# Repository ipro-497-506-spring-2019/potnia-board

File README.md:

# potnia-board
These are the KiCad files for Potnia's PCB.

Release schedule:

|   Version |   Description |   Projected Date | ☑? |
| --------- |   ----------- |   -------------- | -- |
| v0| Super alpha |                                 March 1, 2019 | ☑ |
| v1| Ready for online review |                     March 8, 2019 | ☐ |
| v2| Ready to be sent off for first-round board |  March 15, 2019| ☐ |
| v3| Final revisions; this is a final board |      April 5, 2019 | ☐ |

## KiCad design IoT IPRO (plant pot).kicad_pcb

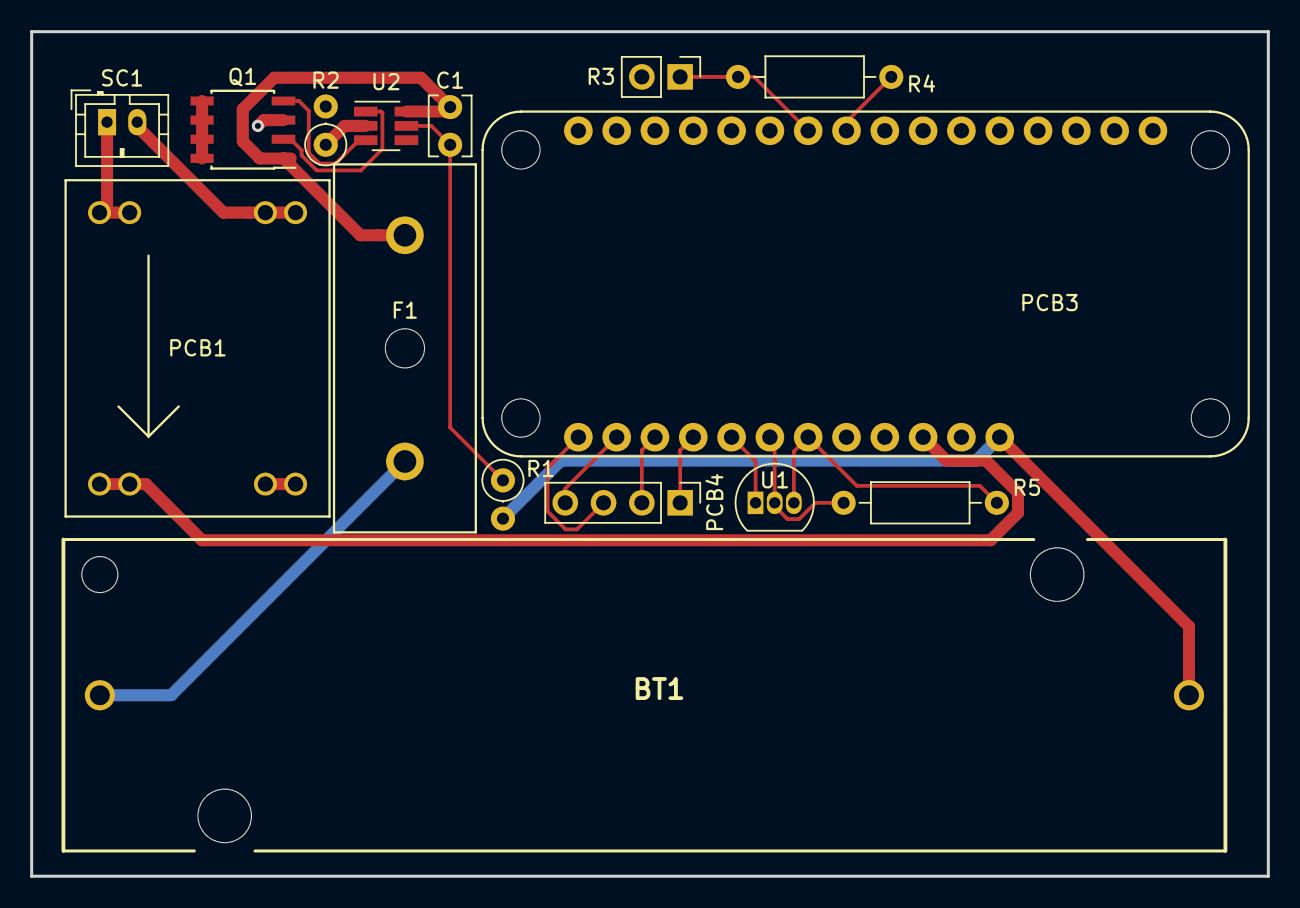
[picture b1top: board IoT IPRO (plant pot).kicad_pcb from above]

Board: 2 copper layers, 82.0 x 56.0 mm, 15 parts (0 on the bottom side), 21 nets.

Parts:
BT1: Battery_Cell; 1043_battery_holder
C1: 100nF; C_Disc_D3.8mm_W2.6mm_P2.50mm
F1: 1A; 0PTF0075P_Littelfuse_5x20mm_holder
PCB1: MP1484EN_board
PCB3: Particle_Argon; argon_tht
PCB4: STEMMA_sensor; PinHeader_1x04_P2.54mm_Vertical
Q1: Q_DUAL_NMOS_S1G1S2G2D1D1D2D2; SOIC-8_3.9x4.9mm_P1.27mm
R1: 330; R_Axial_DIN0207_L6.3mm_D2.5mm_P2.54mm_Vertical
R2: 2.7k; R_Axial_DIN0207_L6.3mm_D2.5mm_P2.54mm_Vertical
R3: 1M; PinHeader_1x02_P2.54mm_Vertical
R4: 10K; R_Axial_DIN0207_L6.3mm_D2.5mm_P10.16mm_Horizontal
R5: 4.7K; R_Axial_DIN0207_L6.3mm_D2.5mm_P10.16mm_Horizontal
SC1: Solar_Cells; JST_PH_B2B-PH-K_1x02_P2.00mm_Vertical
U1: DS18S20; TO-92_Inline
U2: AP9101C-SOT26; SOT-23-6_Handsoldering

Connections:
+5V: PCB1.3, PCB3.26
+BATT: BT1.1, PCB3.28, R1.2
GND: PCB1.4, PCB3.4, Q1.3, R2.2, R3.2
unnamed: BT1.2, F1.1
unnamed: C1.1, R1.1, U2.5
unnamed: C1.2, F1.2, Q1.1, U2.6
unnamed: PCB1.1, SC1.2
unnamed: PCB1.2, SC1.1
unnamed: PCB3.9, R4.1
unnamed: PCB3.10, R3.1, R4.2
unnamed: PCB3.17, PCB4.3
unnamed: PCB3.18, PCB4.4
unnamed: PCB3.19, PCB4.2
unnamed: PCB3.20, PCB4.1
unnamed: PCB3.21, U1.1
unnamed: PCB3.22, R5.2, U1.2
unnamed: PCB3.23, R5.1, U1.3
unnamed: Q1.2, U2.1
unnamed: Q1.4, U2.3
unnamed: Q1.5, Q1.6, Q1.7, Q1.8
unnamed: R2.1, U2.2

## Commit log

2019-03-01 Initial commit
    Add in existing files up to March 1. This is v0 of the board - no over-discharge protection, no Argon, etc.
2019-03-01 Remove unused 1043 library
2019-03-02 Adjust battery holder footprint
2019-03-03 Add undervoltage protection
2019-03-03 Add footprints to undervoltage chips
2019-03-04 Fix symbol definition location
2019-03-04 Add Argon symbol
2019-03-04 Add Argon footprint
2019-03-04 Add schematic sheet info
2019-03-05 Change Photon->Argon in schematic, add flawed over-discharge protection
2019-03-05 Add AP9101C protection symbol
2019-03-05 Remove accidental Eagle export
2019-03-05 Add FET symbols for DMN2029USD
2019-03-05 Add new battery PCM to schematic
2019-03-05 Add footprints
2019-03-06 Add datasheets
2019-03-06 Fix Argon footprint
2019-03-06 Redo PCB. Tracks too thin right now
2019-03-06 Adjust trace widths
2019-03-07 Fix incorrect MOSFET pins
2019-03-07 Update PCB, PDFs
2019-03-07 Improve subcircuit symbols
2019-03-07 Schematic: change barrel jack to solar cells
2019-03-07 Schematic: remove redundant charger
2019-03-07 Schematic: change solar cell footprint to actual port
2019-03-07 Redo board layout
2019-03-07 Rearrange silkscreen labels
2019-03-08 Update PDFs
2019-03-08 Switch AP9101C to SOT-26 :(
2019-03-09 Generate v1 Gerbers
2019-04-12 Tweak voltage divider position
2019-04-12 Remove thru-holes on Argon corners
2019-04-12 Update battery holder footprint
2019-04-12 Update PCB with new battery holder, U2 footprint
2019-04-17 Add schematic test points
2019-04-17 Add SPV1040 symbol
2019-04-18 Move GND pin on SPV1040
2019-04-18 Add SPV1040, batt switches for Argon, charger
2019-04-18 Add some footprints
2019-04-18 Attach i2c directly to power, not GPIO
2019-04-18 Add inductor, DIP switch
2019-04-18 Fix some ERC errors
2019-04-19 Fix power flag error
